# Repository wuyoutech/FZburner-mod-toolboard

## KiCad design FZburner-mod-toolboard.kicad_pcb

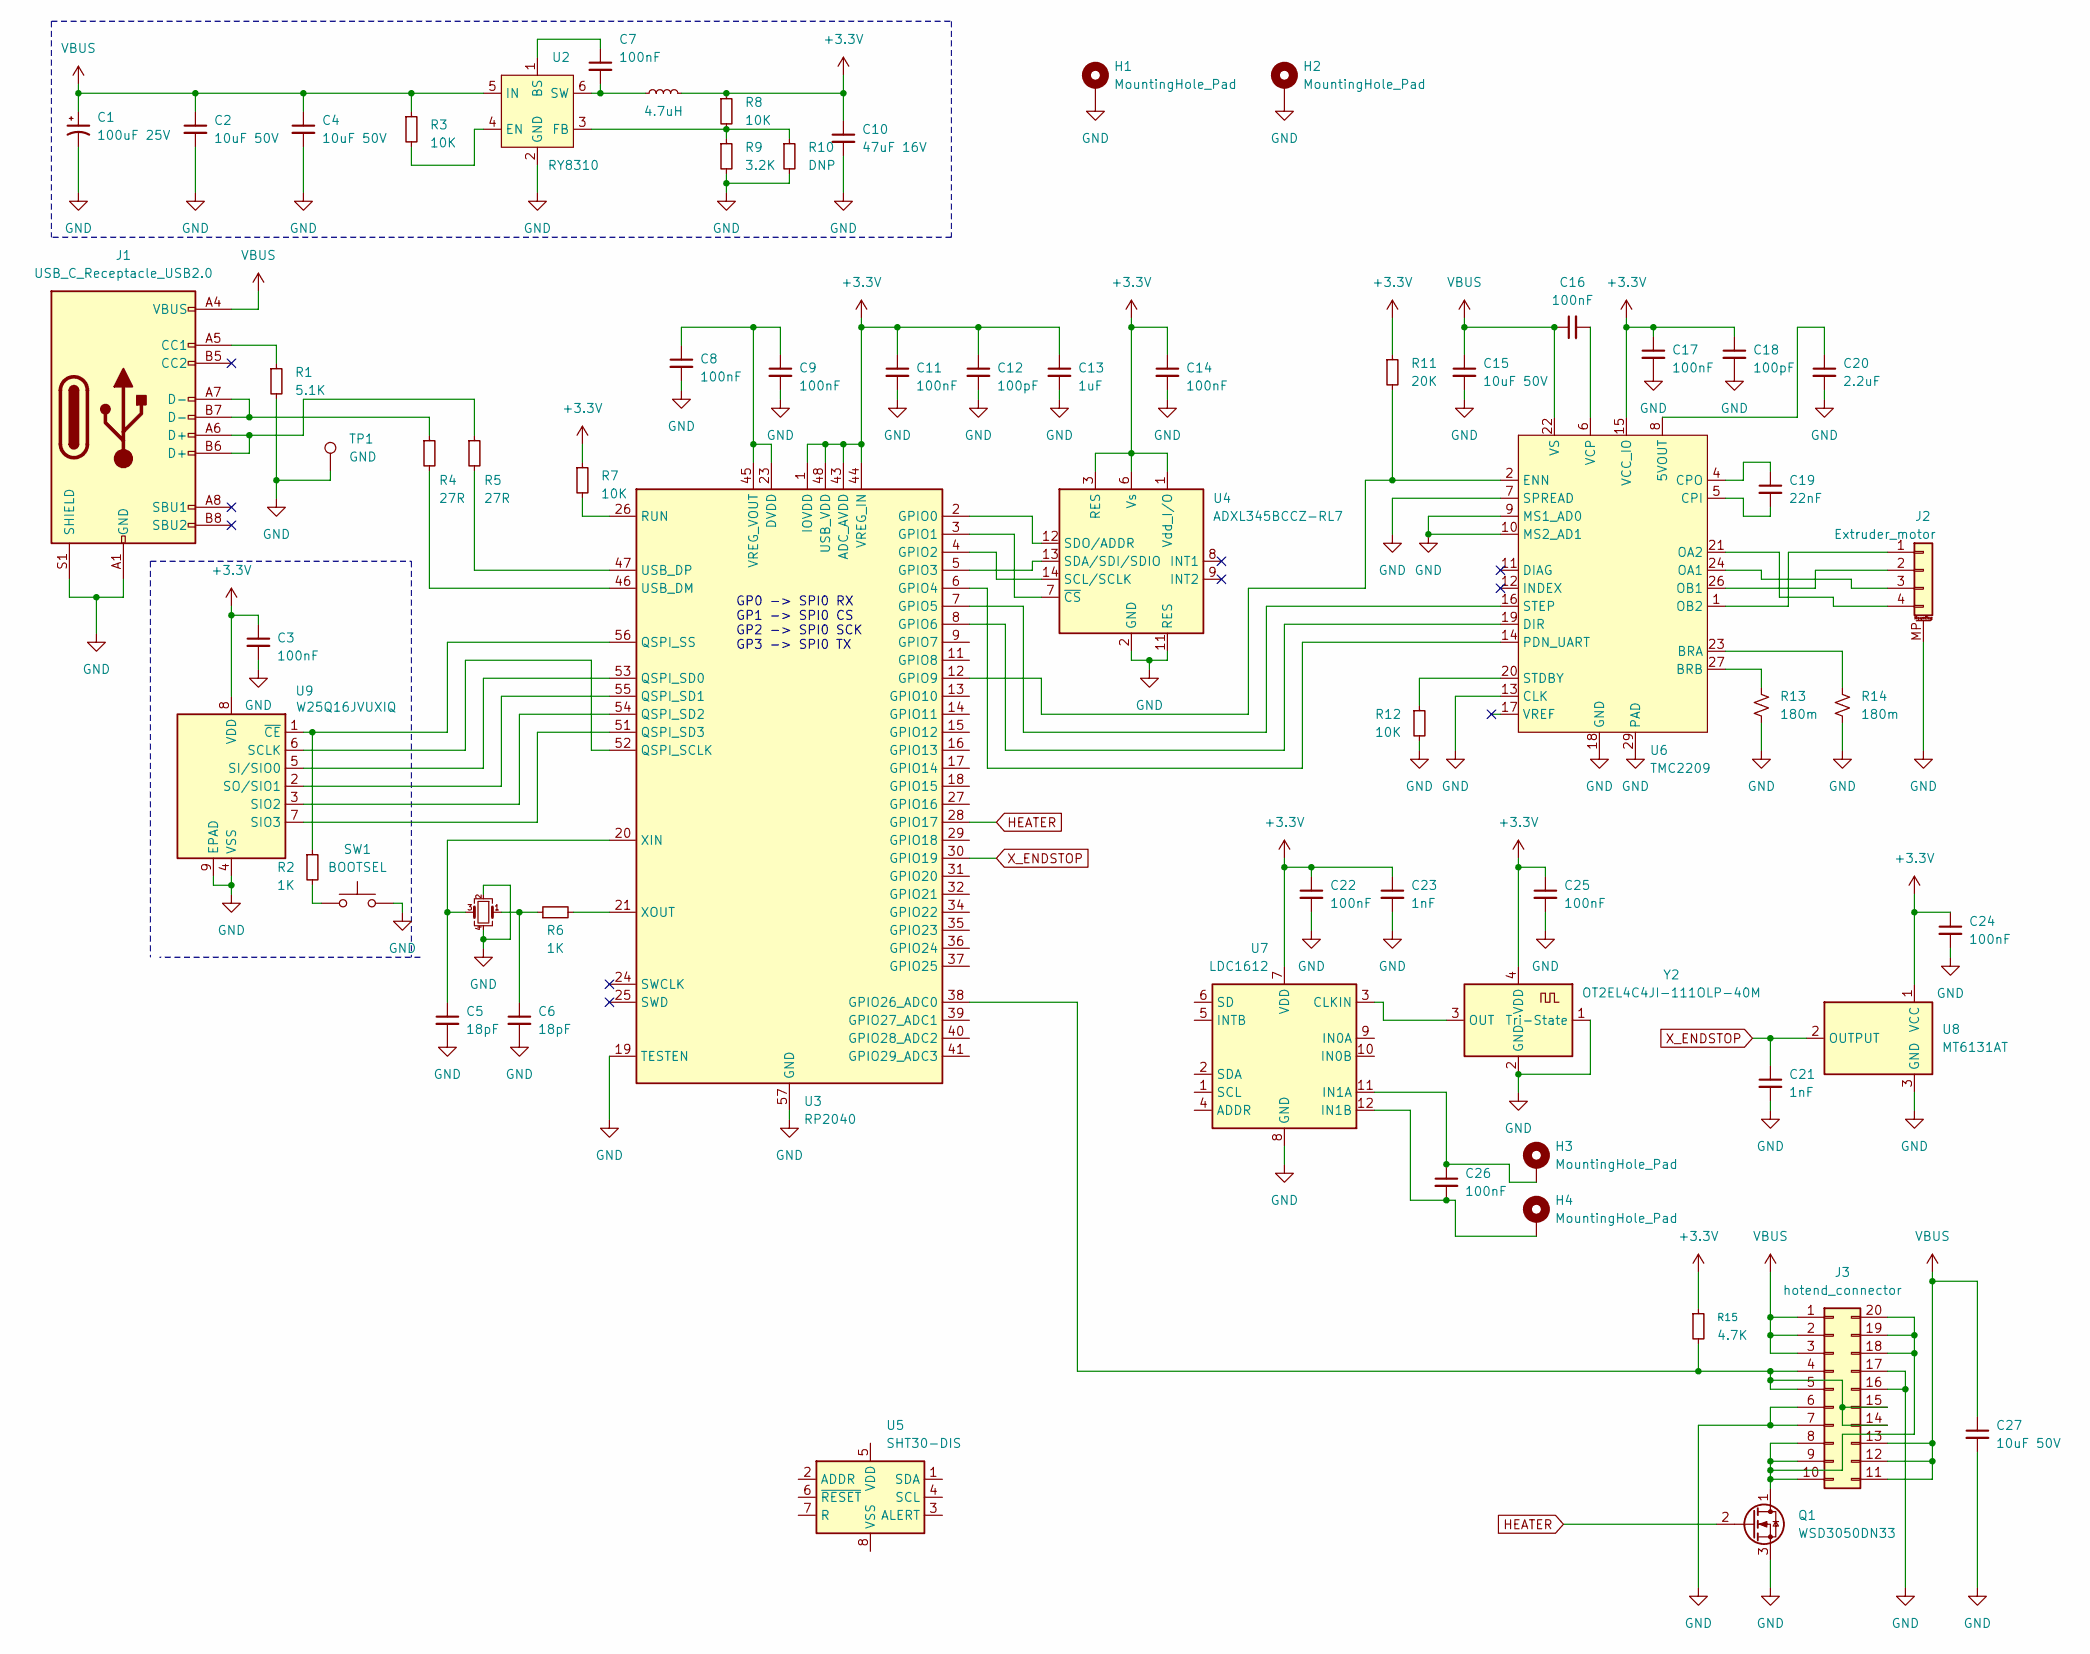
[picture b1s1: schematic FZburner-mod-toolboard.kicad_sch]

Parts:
C1: 100uF 25V; CP_Elec_6.3x5.8
C2, C4, C15, C27: 10uF 50V; C_1210_3225Metric
C3, C7, C8, C9, C11, C14, C16, C17, C22, C24, C25, C26: 100nF; C_0402_1005Metric
C5, C6: 18pF; C_0402_1005Metric
C10: 47uF 16V; C_1210_3225Metric
C12, C18: 100pF; C_0402_1005Metric
C13: 1uF; C_0402_1005Metric
C19: 22nF; C_0402_1005Metric
C20: 2.2uF; C_0402_1005Metric
C21, C23: 1nF; C_0402_1005Metric
H1, H2, H3, H4: MountingHole_Pad; MountingHole_3.2mm_M3_Pad_Via
J1: USB_C_Receptacle_USB2.0; USB_C_Receptacle_G-Switch_GT-USB-7010ASV
J2: Extruder_motor; JST_GH_BM04B-GHS-TBT_1x04-1MP_P1.25mm_Vertical
J3: hotend_connector; 无标题
L1: 4.7uH; L_1008_2520Metric
Q1: WSD3050DN33; SOT-23
R1: 5.1K; R_0402_1005Metric
R2, R6: 1K; R_0402_1005Metric
R3, R7, R8, R12: 10K; R_0402_1005Metric
R4, R5: 27R; R_0402_1005Metric
R9: 3.2K; R_0402_1005Metric
R10: DNP; R_0402_1005Metric
R11: 20K; R_0402_1005Metric
R13, R14: 180m; R_1206_3216Metric
R15: 4.7K; R_0402_1005Metric
SW1: BOOTSEL; SW_SPST_CK_RS282G05A3
TP1: GND; TestPoint_Pad_1.5x1.5mm
U2: RY8310; SOT-23-6
U3: RP2040; QFN-56-1EP_7x7mm_P0.4mm_EP3.2x3.2mm
U4: ADXL345BCCZ-RL7; LGA-14_3x5mm_P0.8mm_LayoutBorder1x6y
U5: SHT30-DIS; Sensirion_DFN-8-1EP_2.5x2.5mm_P0.5mm_EP1.1x1.7mm
U6: TMC2209; QFN-28-1EP_5x5mm_P0.5mm_EP3.75x3.75mm
U7: LDC1612; WSON-12-1EP_4x4mm_P0.5mm_EP2.6x3mm_ThermalVias
U8: MT6131AT; SOT-23
U9: W25Q16JVUXIQ; Winbond_USON-8-1EP_3x2mm_P0.5mm_EP0.2x1.6mm
Y1: 12MHz; Oscillator_SMD_Kyocera_KC2520Z-4Pin_2.5x2.0mm
Y2: OT2EL4C4JI-111OLP-40M; Crystal_SMD_3225-4Pin_3.2x2.5mm

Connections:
+3.3V: C3.1, C10.1, C11.1, C12.1, C13.1, C14.1, C17.1, C18.1, C22.1, C23.1, C24.1, C25.1, L1.2, R7.1, R8.1, R11.1, R15.1, U3.1 (IOVDD), U3.10 (IOVDD), U3.22 (IOVDD), U3.33 (IOVDD), U3.42 (IOVDD), U3.43 (ADC_AVDD), U3.44 (VREG_IN), U3.48 (USB_VDD), U3.49 (IOVDD), U4.1 (Vdd_I/O), U4.3 (RES), U4.6 (Vs), U6.15 (VCC_IO), U7.7 (VDD), U8.1 (VCC), U9.8 (VDD), Y2.4 (VDD)
GND: C1.2, C2.2, C3.2, C4.2, C5.2, C6.2, C8.2, C9.2, C10.2, C11.2, C12.2, C13.2, C14.2, C15.2, C17.2, C18.2, C20.2, C21.2, C22.2, C23.2, C24.2, C25.2, C27.2, H1.1, H2.1, J1.A1 (GND), J1.A12 (GND), J1.B1 (GND), J1.B12 (GND), J1.S1 (SHIELD), J2.MP (MountPin), J3.6, J3.7, J3.16, J3.17, Q1.3 (S), R1.2, R9.2, R10.2, R12.2, R13.2, R14.2, SW1.1, TP1.1, U2.2 (GND), U3.19 (TESTEN), U3.57 (GND), U4.2 (GND), U4.4 (GND), U4.5 (GND), U4.11 (RES), U6.3 (GND), U6.7 (SPREAD), U6.9 (MS1_AD0), U6.10 (MS2_AD1), U6.13 (CLK), U6.18 (GND), U6.29 (PAD), U7.8 (GND), U7.13 (GND), U8.3 (GND), U9.4 (VSS), U9.9 (EPAD), Y1.2, Y1.4, Y2.1 (Tri-State), Y2.2 (GND)
HEATER: Q1.2 (G), U3.28 (GPIO17)
unnamed: C6.1, R6.1, Y1.1
unnamed: J1.A5 (CC1), R1.1
unnamed: J1.A6 (D+), J1.B6 (D+), R5.1
unnamed: J1.A7 (D-), J1.B7 (D-), R4.1
unnamed: J2.1, U6.1 (OB2)
unnamed: J2.2, U6.26 (OB1)
unnamed: J2.3, U6.24 (OA1)
unnamed: J2.4, U6.21 (OA2)
unnamed: J3.8, J3.9, J3.10, J3.18, J3.19, J3.20, Q1.1 (D)
unnamed: J3.4, J3.5, J3.14, J3.15, R15.2, U3.38 (GPIO26_ADC0)
unnamed: R2.2, SW1.2
unnamed: C7.1, U2.1 (BS)
unnamed: R3.2, U2.4 (EN)
unnamed: R8.2, R9.1, R10.1, U2.3 (FB)
unnamed: C7.2, L1.1, U2.6 (SW)
unnamed: U3.2 (GPIO0), U4.12 (SDO/ADDR)
unnamed: U3.3 (GPIO1), U4.7 (~CS)
unnamed: U3.4 (GPIO2), U4.14 (SCL/SCLK)
unnamed: U3.5 (GPIO3), U4.13 (SDA/SDI/SDIO)
unnamed: U3.6 (GPIO4), U6.14 (PDN_UART)
unnamed: U3.7 (GPIO5), U6.16 (STEP)
unnamed: U3.8 (GPIO6), U6.19 (DIR)
unnamed: R11.2, U3.12 (GPIO9), U6.2 (ENN)
unnamed: U3.52 (QSPI_SCLK), U9.6 (SCLK)
unnamed: U3.53 (QSPI_SD0), U9.5 (SI/SIO0)
unnamed: U3.55 (QSPI_SD1), U9.2 (SO/SIO1)
unnamed: U3.54 (QSPI_SD2), U9.3 (SIO2)
unnamed: U3.51 (QSPI_SD3), U9.7 (SIO3)
unnamed: R2.1, U3.56 (QSPI_SS), U9.1 (~CE)
unnamed: R7.2, U3.26 (RUN)
unnamed: R4.2, U3.46 (USB_DM)
unnamed: R5.2, U3.47 (USB_DP)
unnamed: C8.1, C9.1, U3.23 (DVDD), U3.45 (VREG_VOUT), U3.50 (DVDD)
unnamed: C5.1, U3.20 (XIN), Y1.3
unnamed: R6.2, U3.21 (XOUT)
unnamed: U5.8 (VSS), U5.9 (VSS)
unnamed: C20.1, U6.8 (5VOUT)
unnamed: R14.1, U6.23 (BRA)
unnamed: R13.1, U6.27 (BRB)
unnamed: C19.2, U6.5 (CPI)
unnamed: C19.1, U6.4 (CPO)
unnamed: R12.1, U6.20 (STDBY)
unnamed: C16.2, U6.6 (VCP)
unnamed: U7.3 (CLKIN), Y2.3 (OUT)
unnamed: C26.1, H3.1, U7.11 (IN1A)
unnamed: C26.2, H4.1, U7.12 (IN1B)
VBUS: C1.1, C2.1, C4.1, C15.1, C16.1, C27.1, J1.A4 (VBUS), J1.A9 (VBUS), J1.B4 (VBUS), J1.B9 (VBUS), J3.1, J3.2, J3.3, J3.11, J3.12, J3.13, R3.1, U2.5 (IN), U6.22 (VS), U6.28 (VS)
X_ENDSTOP: C21.1, U3.30 (GPIO19), U8.2 (OUTPUT)

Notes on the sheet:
GP0 -> SPI0 RX GP1 -> SPI0 CS GP2 -> SPI0 SCK GP3 -> SPI0 TX

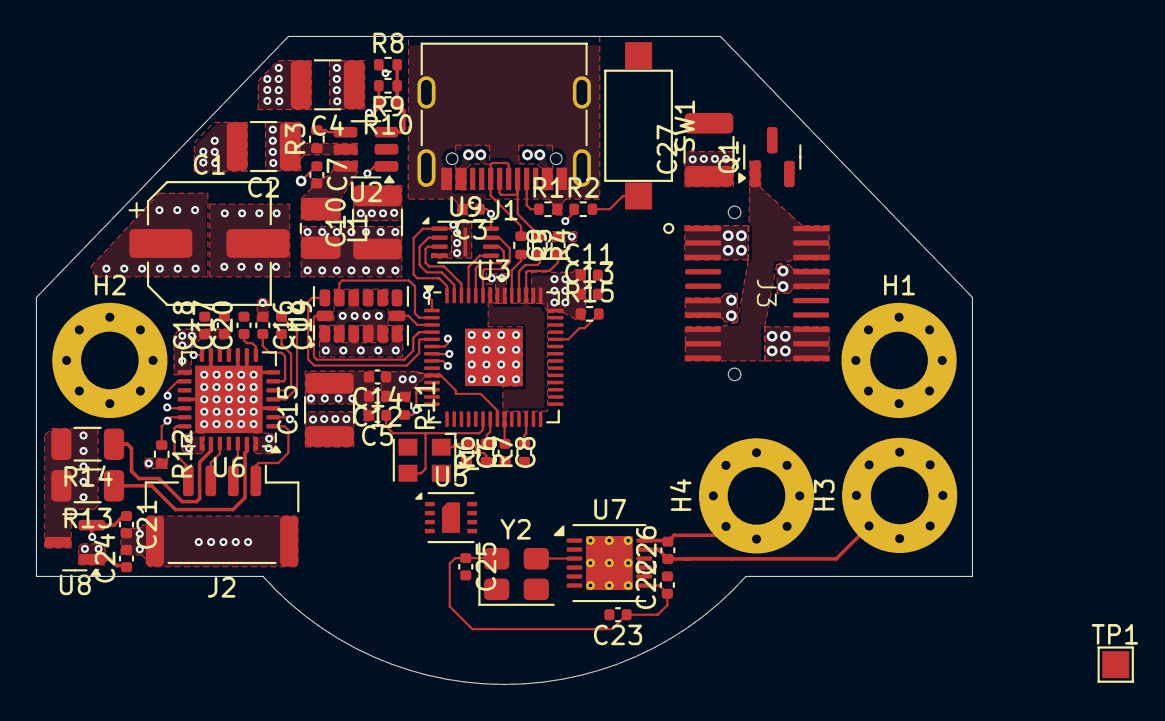
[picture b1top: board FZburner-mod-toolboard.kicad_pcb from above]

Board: 4 copper layers, 52.0 x 36.0 mm, 63 parts (0 on the bottom side), 51 nets.

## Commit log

2025-12-23 temp commit
2025-12-24 temp_commit
